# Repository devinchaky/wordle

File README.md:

# wordle
Wordle game programmed using embedded C for TM4C Micro-controller. Repository contains all of the C and header files for project, as well as custom PCB design files.

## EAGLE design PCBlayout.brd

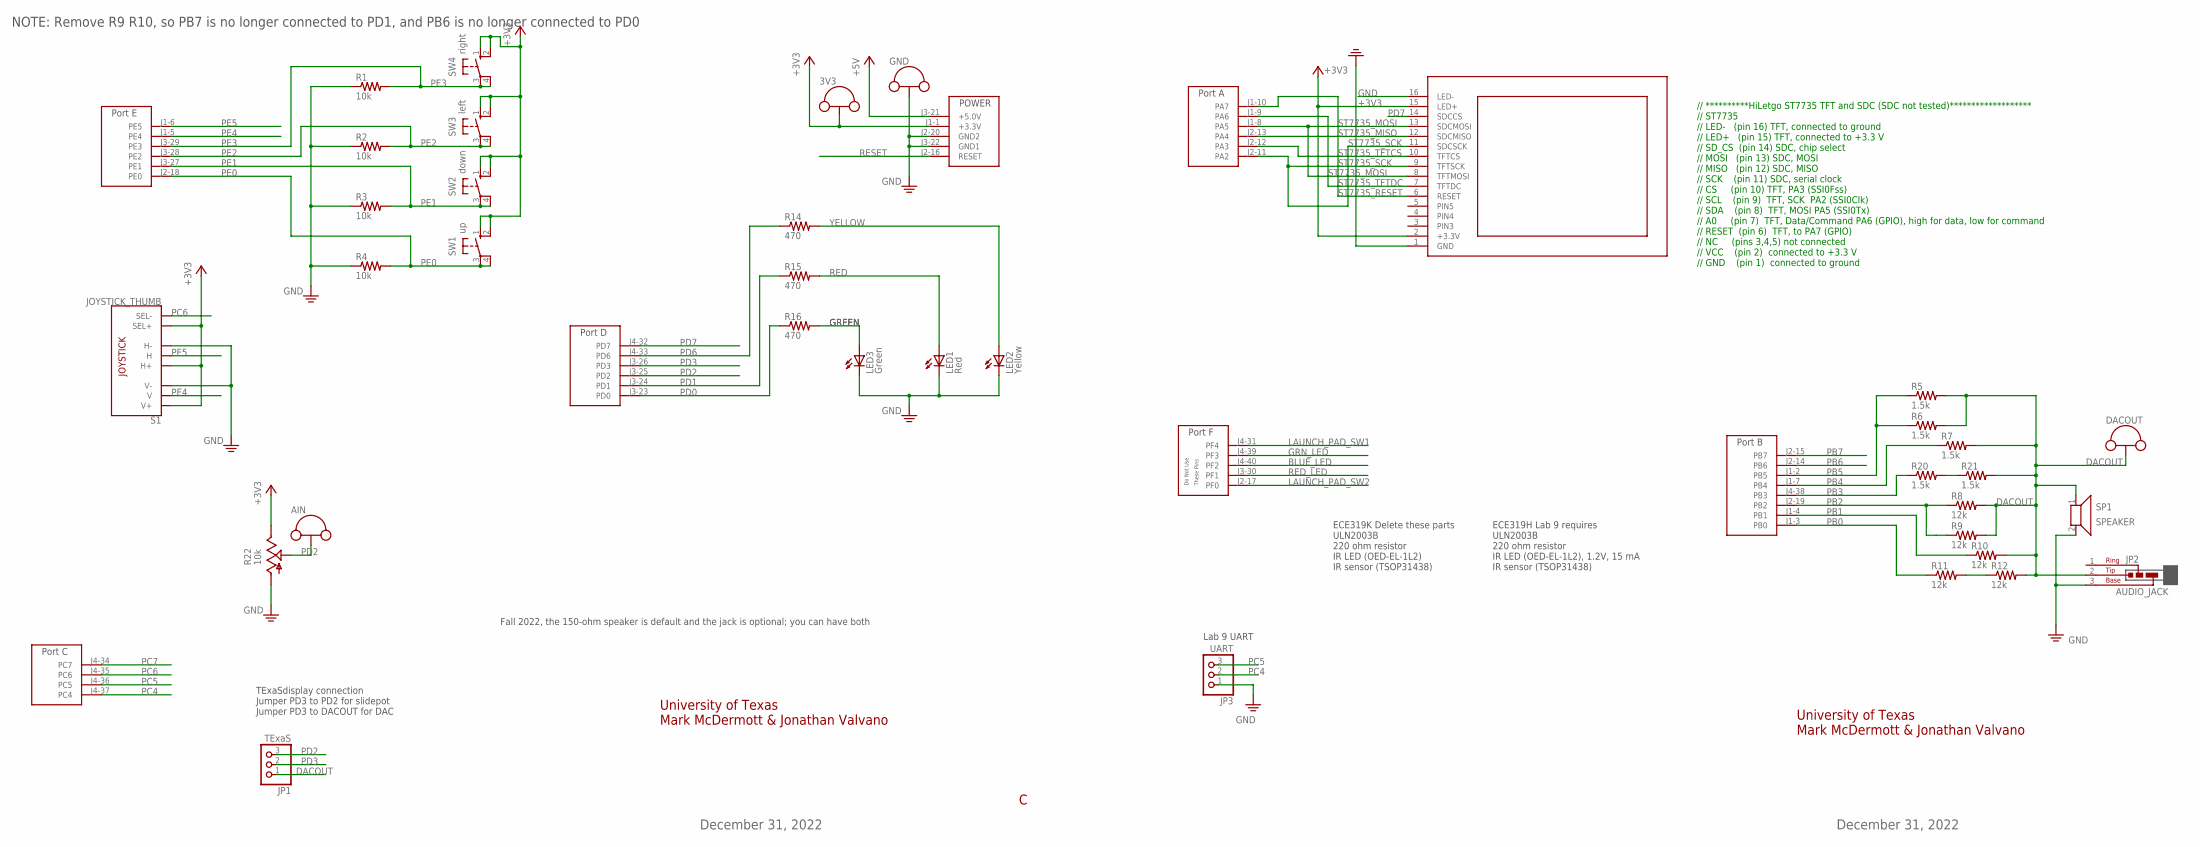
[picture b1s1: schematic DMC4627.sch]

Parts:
3V3: TP_LOOP
AIN: TP_LOOP
DACOUT: TP_LOOP
GND: TP_LOOP
JP1: TExaS; 1X03
JP2: AUDIO_JACK; JACK
JP3: UART; 1X03
LED1: Red; LED5MM
LED2: Yellow; LED5MM
LED3: Green; LED5MM
R1, R2, R3, R4: 10k; RES300MIL
R5, R6, R7, R20, R21: 1.5k; RES300MIL
R8, R9, R10, R11, R12: 12k; RES300MIL
R14, R15, R16: 470; RES300MIL
R22: 10k; PTA2043
S1: JOYSTICK_THUMB; JOYSTICK
SP1: SPEAKER; 1X02
ST7735_LCD: HILETGO
SW1: up; B3F-10XX
SW2: down; B3F-10XX
SW3: left; B3F-10XX
SW4: right; B3F-10XX
U$2: TM4C_BP; TM4C_BOOSTER_PACK

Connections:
+3V3: 3V3.P$1, 3V3.P$2, R22.1 (E), S1.B1A (SEL+), S1.H1 (H+), S1.V1 (V+), ST7735_LCD.2 (+3.3V), ST7735_LCD.15 (LED+), SW1.1 (S), SW1.2 (S1), SW2.1 (S), SW2.2 (S1), SW3.1 (S), SW3.2 (S1), SW4.1 (S), SW4.2 (S1), U$2.J1-1 (+3.3V)
+5V: U$2.J3-21 (+5.0V)
BLUE_LED: U$2.J4-40 (PF2)
DACOUT: DACOUT.P$1, DACOUT.P$2, JP1.1, JP2.2 (TIP), R5.2, R6.2, R7.2, R8.2, R9.2, R10.2, R12.2, R21.2, SP1.1
GND: GND.P$1, GND.P$2, JP2.3 (BASE), JP3.1, LED1.K (C), LED2.K (C), LED3.K (C), R1.1, R2.1, R3.1, R4.1, R22.3 (A), S1.H3 (H-), S1.V3 (V-), SP1.2, ST7735_LCD.1 (GND), ST7735_LCD.16 (LED-), U$2.J2-20 (GND2), U$2.J3-22 (GND1)
GREEN: LED3.A, R16.2
GRN_LED: U$2.J4-39 (PF3)
LAUNCH_PAD_SW1: U$2.J4-31 (PF4)
LAUNCH_PAD_SW2: U$2.J2-17 (PF0)
PB0: R11.1, U$2.J1-3 (PB0)
PB1: R10.1, U$2.J1-4 (PB1)
PB2: R8.1, R9.1, U$2.J2-19 (PB2)
PB3: R20.1, U$2.J4-38 (PB3)
PB4: R7.1, U$2.J1-7 (PB4)
PB5: R5.1, R6.1, U$2.J1-2 (PB5)
PB6: U$2.J2-14 (PB6)
PB7: U$2.J2-15 (PB7)
PC4: JP3.2, U$2.J4-37 (PC4)
PC5: JP3.3, U$2.J4-36 (PC5)
PC6: S1.B2A (SEL-), U$2.J4-35 (PC6)
PC7: U$2.J4-34 (PC7)
PD0: R16.1, U$2.J3-23 (PD0)
PD1: R15.1, U$2.J3-24 (PD1)
PD2: AIN.P$1, AIN.P$2, JP1.3, R22.2 (S), U$2.J3-25 (PD2)
PD3: JP1.2, U$2.J3-26 (PD3)
PD6: R14.1, U$2.J4-33 (PD6)
PD7: ST7735_LCD.14 (SDCCS), U$2.J4-32 (PD7)
PE0: R4.2, SW1.3, SW1.4 (P1), U$2.J2-18 (PE0)
PE1: R3.2, SW2.3, SW2.4 (P1), U$2.J3-27 (PE1)
PE2: R2.2, SW3.3, SW3.4 (P1), U$2.J3-28 (PE2)
PE3: R1.2, SW4.3, SW4.4 (P1), U$2.J3-29 (PE3)
PE4: S1.V2 (V), U$2.J1-5 (PE4)
PE5: S1.H2 (H), U$2.J1-6 (PE5)
R11_R12: R11.2, R12.1
R20_R21: R20.2, R21.1
RED: LED1.A, R15.2
RED_LED: U$2.J3-30 (PF1)
RESET: U$2.J2-16 (RESET)
ST7735_MISO: ST7735_LCD.12 (SDCMISO), U$2.J2-13 (PA4)
ST7735_MOSI: ST7735_LCD.8 (TFTMOSI), ST7735_LCD.13 (SDCMOSI), U$2.J1-8 (PA5)
ST7735_RESET: ST7735_LCD.6 (RESET), U$2.J1-10 (PA7)
ST7735_SCK: ST7735_LCD.9 (TFTSCK), ST7735_LCD.11 (SDCSCK), U$2.J2-11 (PA2)
ST7735_TFTCS: ST7735_LCD.10 (TFTCS), U$2.J2-12 (PA3)
ST7735_TFTDC: ST7735_LCD.7 (TFTDC), U$2.J1-9 (PA6)
YELLOW: LED2.A, R14.2

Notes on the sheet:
University of Texas Mark McDermott & Jonathan Valvano
December 31, 2022
NOTE: Remove R9 R10, so PB7 is no longer connected to PD1, and PB6 is no longer connected to PD0
TExaSdisplay connection Jumper PD3 to PD2 for slidepot Jumper PD3 to DACOUT for DAC
Lab 9 UART
Fall 2022, the 150-ohm speaker is default and the jack is optional; you can have both
ECE319H Lab 9 requires ULN2003B 220 ohm resistor IR LED (OED-EL-1L2), 1.2V, 15 mA IR sensor (TSOP31438)
ECE319K Delete these parts ULN2003B 220 ohm resistor IR LED (OED-EL-1L2) IR sensor (TSOP31438)
// **********HiLetgo ST7735 TFT and SDC (SDC not tested)******************* // ST7735 // LED- (pin 16) TFT, connected to ground // LED+ (pin 15) TFT, connected to +3.3 V // SD_CS (pin 14) SDC, chip select // MOSI (pin 13) SDC, MOSI // MISO (pin 12) SDC, MISO // SCK (pin 11) SDC, serial clock // CS 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

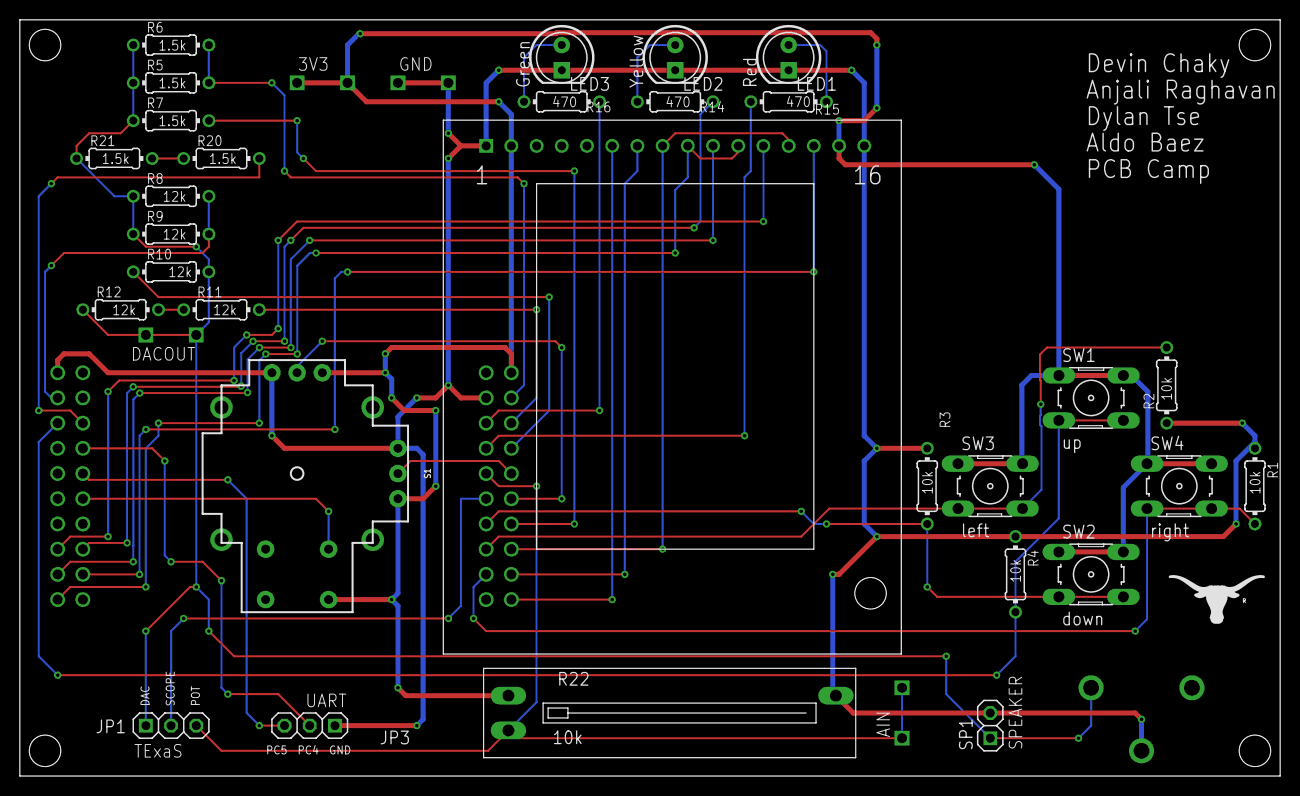
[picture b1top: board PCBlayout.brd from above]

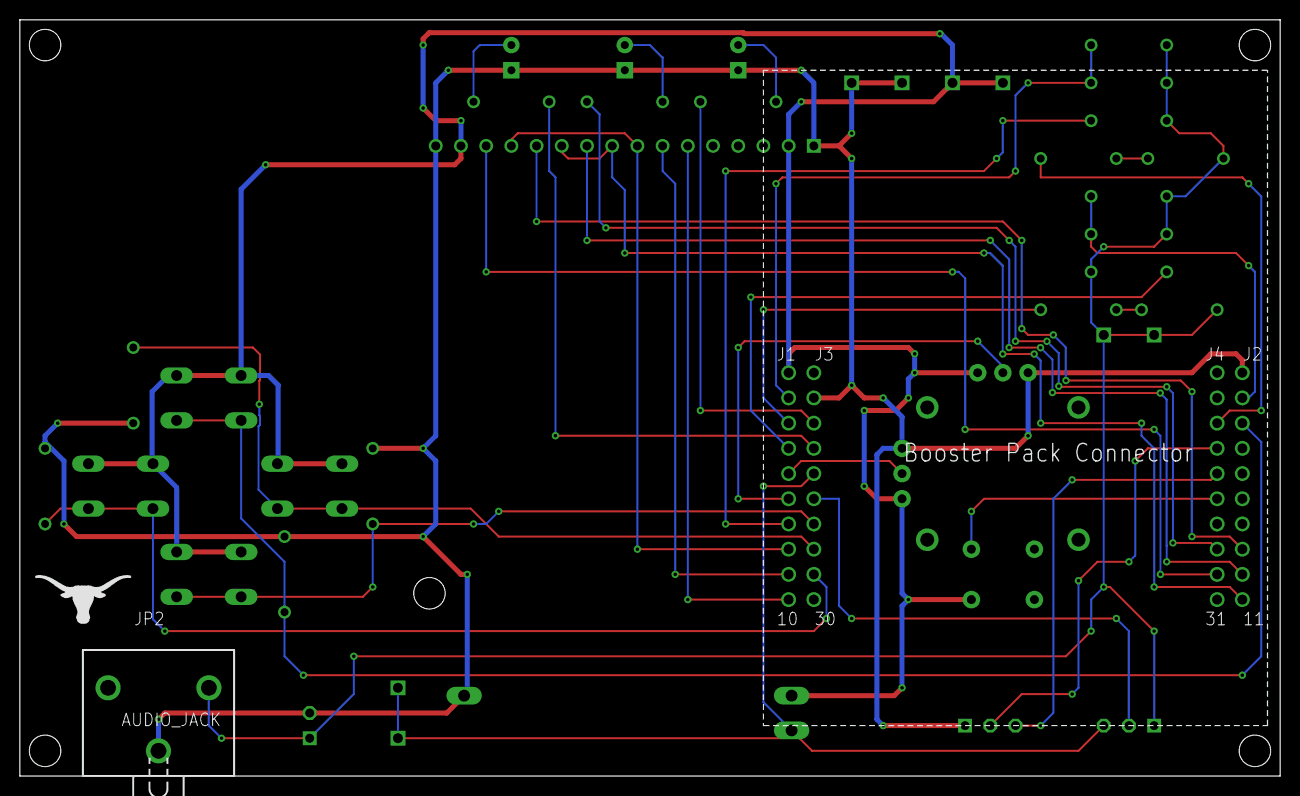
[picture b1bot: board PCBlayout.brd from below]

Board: 2 copper layers, 127.0 x 76.2 mm, 36 parts (2 on the bottom side), 35 nets.

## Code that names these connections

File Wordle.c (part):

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
// ******* Possible Hardware I/O connections*******************
// Slide pot pin 1 connected to ground
// Slide pot pin 2 connected to PD2/AIN5
// Slide pot pin 3 connected to +3.3V 
// buttons connected to PE0-PE3
// 32*R resistor DAC bit 0 on PB0 (least significant bit)
// 16*R resistor DAC bit 1 on PB1
// 8*R resistor DAC bit 2 on PB2 
// 4*R resistor DAC bit 3 on PB3
// 2*R resistor DAC bit 4 on PB4
// 1*R resistor DAC bit 5 on PB5 (most significant bit)
// LED on PD1
// LED on PD0


#include <stdint.h>
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//------------Switch_Debounce------------
// Read and return the status of the switch 
// Input: none
// Output: 0x02 if PB1 is high
//         0x00 if PB1 is low
// debounces switch
uint32_t Switch_Debounce(void){
uint32_t in,old,time; 
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
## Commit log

2023-07-13 Upload project files
2023-07-13 Rename DMC4627.sch to PCBschematic.sch
2023-07-13 Rename DMC4627.brd to PCBlayout.brd

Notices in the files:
parts and their libraries:
SparkFun-Switches: Licensing: Creative Commons ShareAlike 4.0 International - https://creativecommons.org/licenses/by-sa/4.0
